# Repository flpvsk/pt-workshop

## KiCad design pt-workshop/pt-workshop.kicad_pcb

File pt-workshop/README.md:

### PTT

PT2399 adapter board for prototyping pedals.

[Schematic](./ptt-v1rev2.pdf)

#### Pins

1. +9V (Input)
2. GND (Input)
3. +4.5 (Input)
4. +5.0V (Output of the on-board 5V regulator)
5. GND (Input)
6. CLK (Ouptut of the PT2399 Clock pin, #5 on the chip)
7. Ref (Output of the PT2399 Ref pin, #2 on the chip)
8. GND (Input)
9. A In (Input for the audio signal)
10. A Out (Output of the processed audio signal)
11. GND (Input)
12. Ic In (Input, this pin is connected to the VCO pin #6 on
    PT2399, it controls delay time, see below for details);
13. Ic Out (Output of the Voltage-to-Current converter);
14. GND;
15. Vtime (Input of the Voltage-to-Current converter).

For minimum operation, please connect these pins. Keep in
mind for duplicate pins like GND, it's sufficient to just
connect one of the pins.

* `Pin 1`: +9V;
* `Pin 2`: GND;
* `Pin 3`: +4.5V;
* `Pin 9`: Audio In;
* `Pin 10`: Audio Out;
* `Pin 12`: Ic In. This pin controls delay time, see below
  for details.

#### Control delay time via a pot

`Ic In` pin (#12) on the adapter board is hooked up directly
to the control pin on the PT2399. The easiest way to vary
delay time is to connect this pin to ground via a
potentiometer, e.g. B100k.

The larger the resistance to GND the longer the delay time.

The minimum necessary resistance to GND on PT2399 startup is
2k. Otherwise the chip latches up. [See details in this Electrosmash article.](https://www.electrosmash.com/pt2399-analysis)

#### Control delay time via voltage

It is possible to control delay time of this board using
voltage instead of a potentiometer. There's an onboard
voltage-to-current converter. To use it, send control
voltage via `Vtime` pin and get the control current via the
`Ic Out` pin. Connect `Ic Out` to `Ic In` to control delay
time using `Vtime`. The lower `Vtime` the longer the delay
time would be.

#### Example minimal delay circuit with repeats

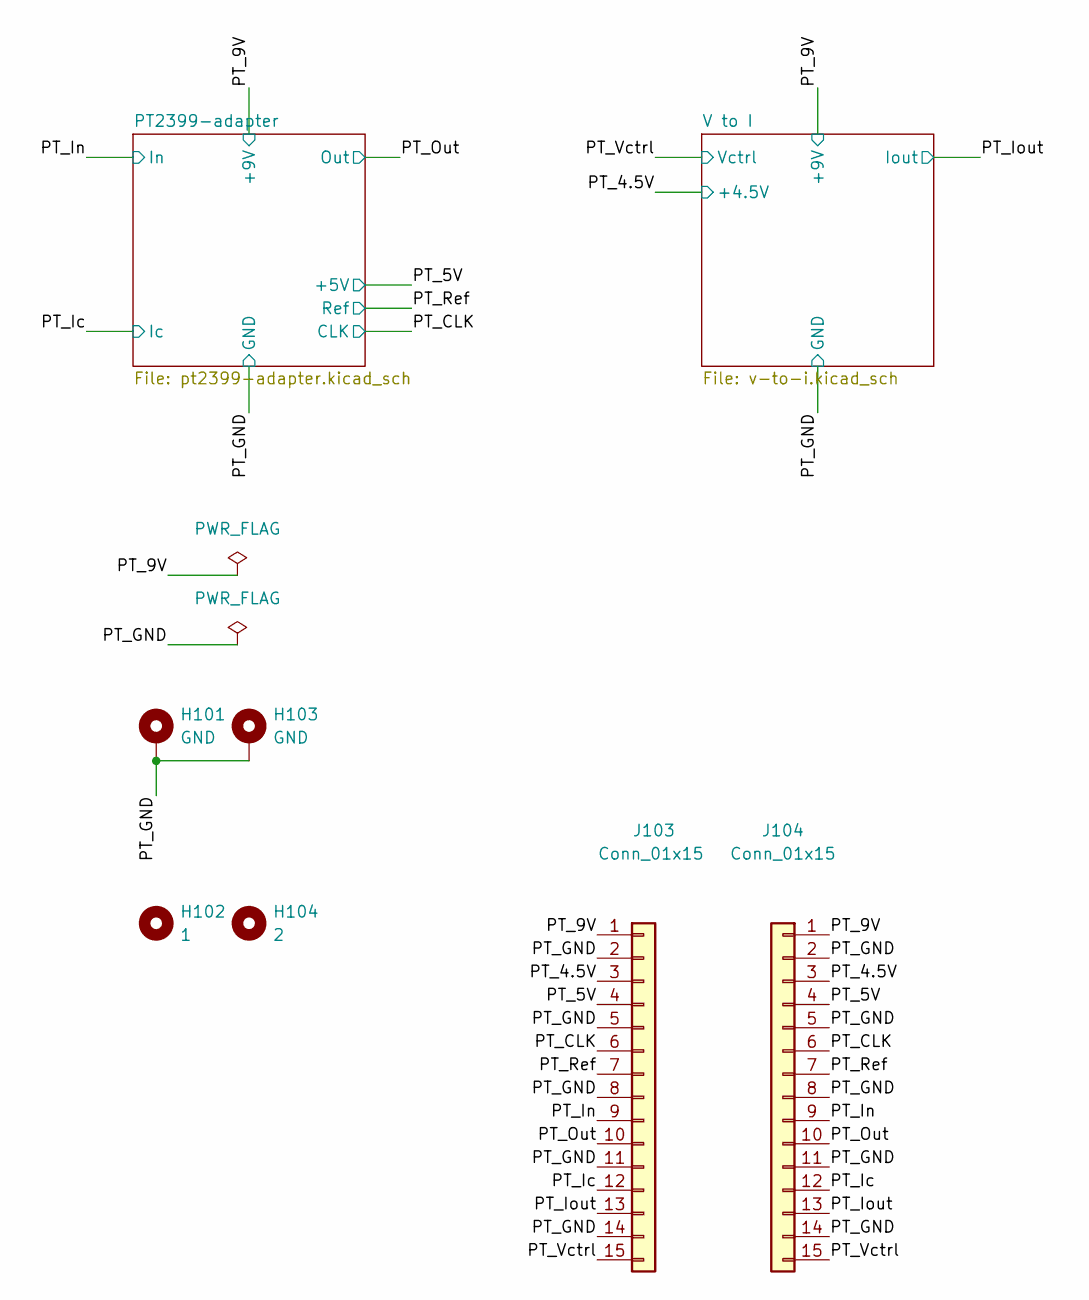
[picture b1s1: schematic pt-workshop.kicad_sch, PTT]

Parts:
H101, H103: GND; MountingHole_3.2mm_M3_ISO14580_Pad
H102: 1; MountingHole_3.2mm_M3
H104: 2; MountingHole_3.2mm_M3
J103, J104: Conn_01x15; PinSocket_1x15_P2.54mm_Vertical

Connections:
/PT_4.5V: J103.3, J104.3; also elsewhere on the board
/PT_5V: J103.4, J104.4; also elsewhere on the board
/PT_9V: J103.1, J104.1; also elsewhere on the board
/PT_CLK: J103.6, J104.6; also elsewhere on the board
/PT_GND: H101.1, H103.1, J103.2, J103.5, J103.8, J103.11, J103.14, J104.2, J104.5, J104.8, J104.11, J104.14; also elsewhere on the board
/PT_Ic: J103.12, J104.12; also elsewhere on the board
/PT_In: J103.9, J104.9; also elsewhere on the board
/PT_Iout: J103.13, J104.13; also elsewhere on the board
/PT_Out: J103.10, J104.10; also elsewhere on the board
/PT_Ref: J103.7, J104.7; also elsewhere on the board
/PT_Vctrl: J103.15, J104.15; also elsewhere on the board

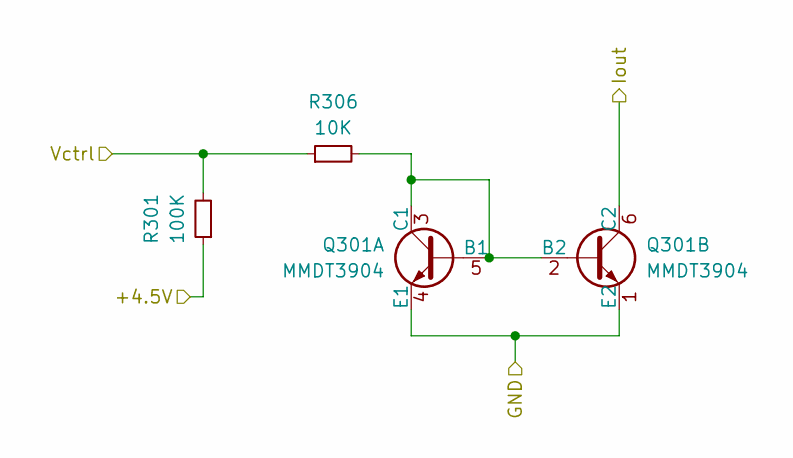
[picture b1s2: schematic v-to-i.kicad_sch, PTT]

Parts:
Q301: MMDT3904; SOT-363_SC-70-6_Handsoldering; LCSC C41375125
R301: 100K; R_0603_1608Metric_Pad0.98x0.95mm_HandSolder; LCSC C25803
R306: 10K; R_0603_1608Metric_Pad0.98x0.95mm_HandSolder; LCSC C25804

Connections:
/PT_4.5V: R301.1; also elsewhere on the board
/PT_GND: Q301.1 (E2), Q301.4 (E1); also elsewhere on the board
/PT_Iout: Q301.6 (C2); also elsewhere on the board
/PT_Vctrl: R301.2, R306.1; also elsewhere on the board
unnamed: Q301.2 (B2), Q301.3 (C1), Q301.5 (B1), R306.2

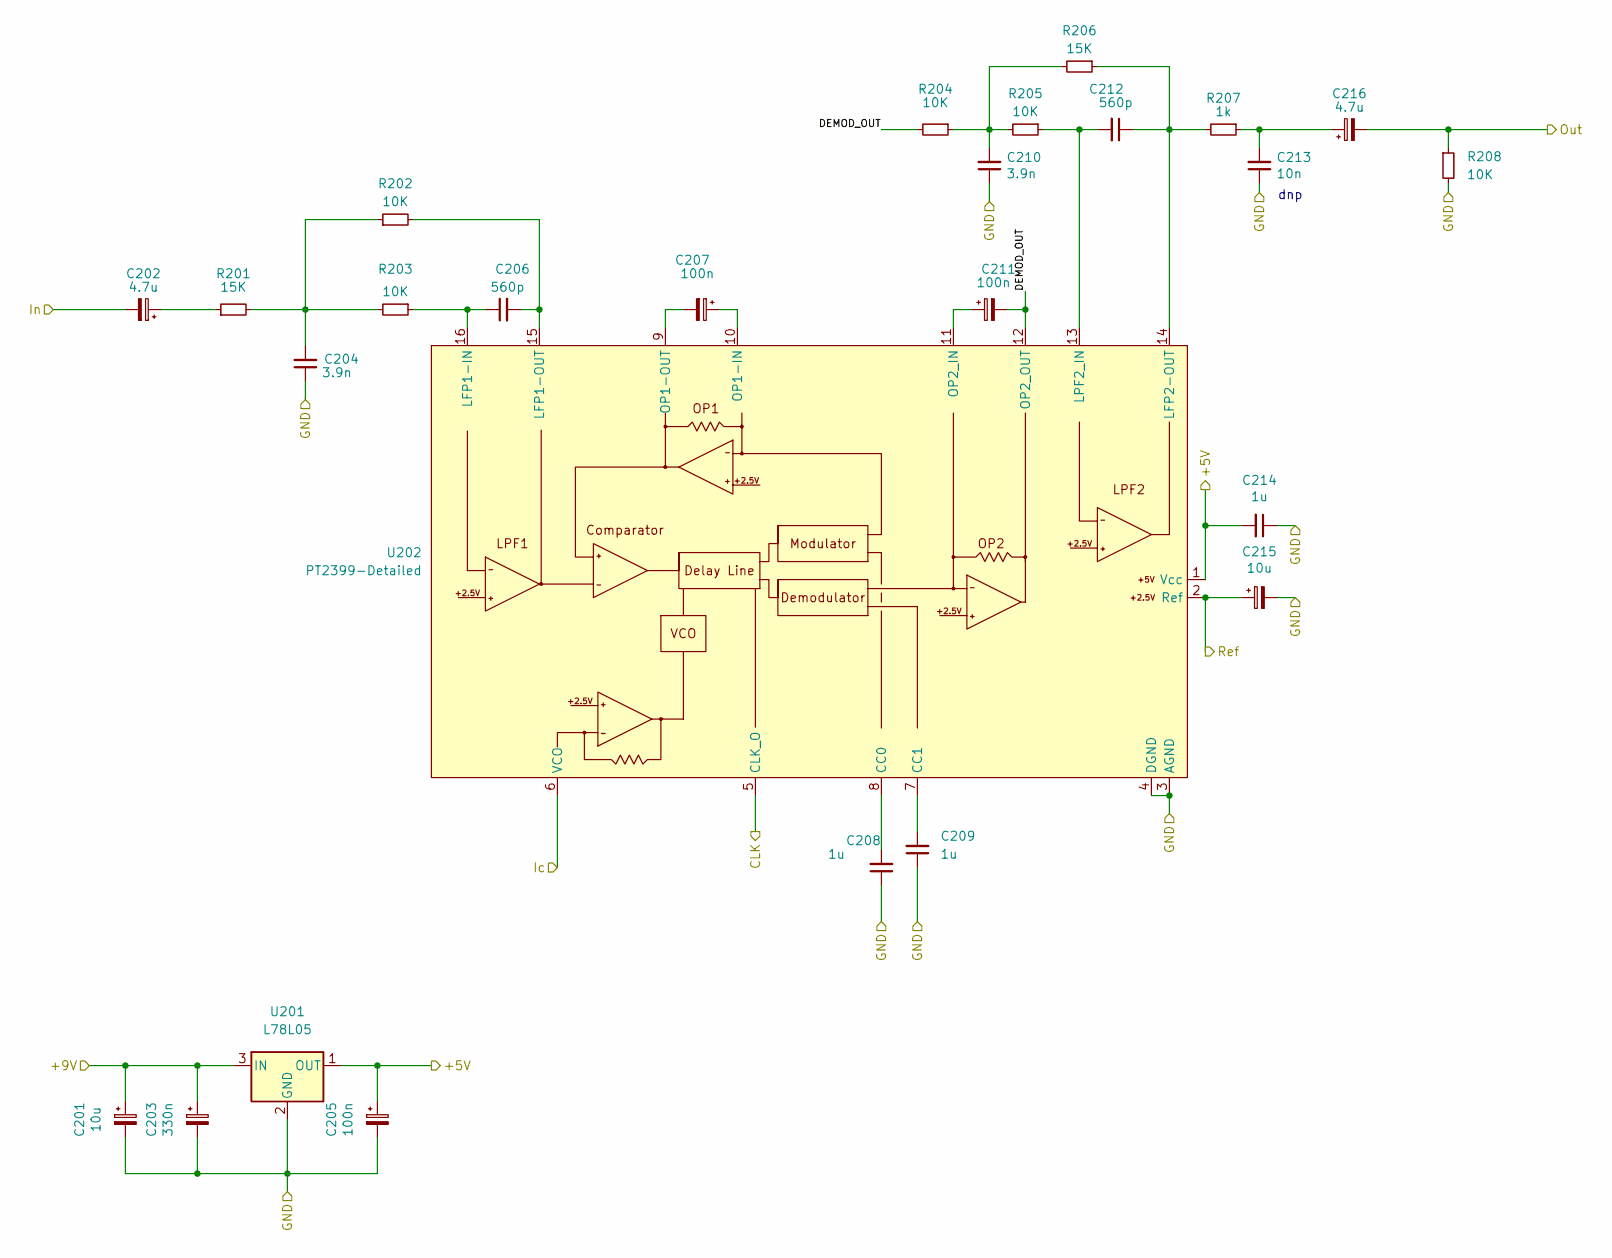
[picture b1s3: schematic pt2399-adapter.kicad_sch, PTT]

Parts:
C201, C215: 10u; CP_EIA-3216-10_Kemet-I_Pad1.58x1.35mm_HandSolder; LCSC C128253
C202, C216: 4.7u; CP_Elec_4x5.4; LCSC C5246584
C203: 330n; CP_EIA-3216-10_Kemet-I_Pad1.58x1.35mm_HandSolder; LCSC C212667
C204, C210: 3.9n; C_0603_1608Metric_Pad1.08x0.95mm_HandSolder; LCSC C415537
C205: 100n; CP_EIA-3216-10_Kemet-I_Pad1.58x1.35mm_HandSolder; LCSC C1952859
C206, C212: 560p; C_0603_1608Metric_Pad1.08x0.95mm_HandSolder; LCSC C694498
C207, C211: 100n; CP_Elec_4x5.4; Mouser 710-865080440002
C208, C209, C214: 1u; C_0603_1608Metric_Pad1.08x0.95mm_HandSolder; LCSC C15849
C213: 10n; C_0603_1608Metric_Pad1.08x0.95mm_HandSolder; LCSC C3836718
R201, R206: 15K; R_0603_1608Metric_Pad0.98x0.95mm_HandSolder; LCSC C22809
R202, R203, R204, R205, R208: 10K; R_0603_1608Metric_Pad0.98x0.95mm_HandSolder; LCSC C25804
R207: 1k; R_0603_1608Metric_Pad0.98x0.95mm_HandSolder; LCSC C21190
U201: L78L05; SOT-89-3; LCSC C42738
U202: PT2399-Detailed; SOIC-16_3.9x9.9mm_P1.27mm; LCSC C126407

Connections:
/PT2399-adapter/DEMOD_OUT: C211.2, R204.2, U202.12 (OP2_OUT)
/PT_5V: C205.1, C214.2, U201.1 (OUT), U202.1 (Vcc); also elsewhere on the board
/PT_9V: C201.1, C203.1, U201.3 (IN); also elsewhere on the board
/PT_CLK: U202.5 (CLK_O); also elsewhere on the board
/PT_GND: C201.2, C203.2, C204.1, C205.2, C208.1, C209.1, C210.1, C213.1, C214.1, C215.2, R208.2, U201.2 (GND), U202.3 (AGND), U202.4 (DGND); also elsewhere on the board
/PT_Ic: U202.6 (VCO); also elsewhere on the board
/PT_In: C202.2; also elsewhere on the board
/PT_Out: C216.2, R208.1; also elsewhere on the board
/PT_Ref: C215.1, U202.2 (Ref); also elsewhere on the board
unnamed: C202.1, R201.1
unnamed: C204.2, R201.2, R202.1, R203.2
unnamed: C206.1, R203.1, U202.16 (LFP1-IN)
unnamed: C206.2, R202.2, U202.15 (LFP1-OUT)
unnamed: C207.1, U202.10 (OP1-IN)
unnamed: C207.2, U202.9 (OP1-OUT)
unnamed: C208.2, U202.8 (CC0)
unnamed: C209.2, U202.7 (CC1)
unnamed: C210.2, R204.1, R205.2, R206.2
unnamed: C211.1, U202.11 (OP2_IN)
unnamed: C212.1, R206.1, R207.2, U202.14 (LFP2-OUT)
unnamed: C212.2, R205.1, U202.13 (LPF2_IN)
unnamed: C213.2, C216.1, R207.1

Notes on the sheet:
dnp

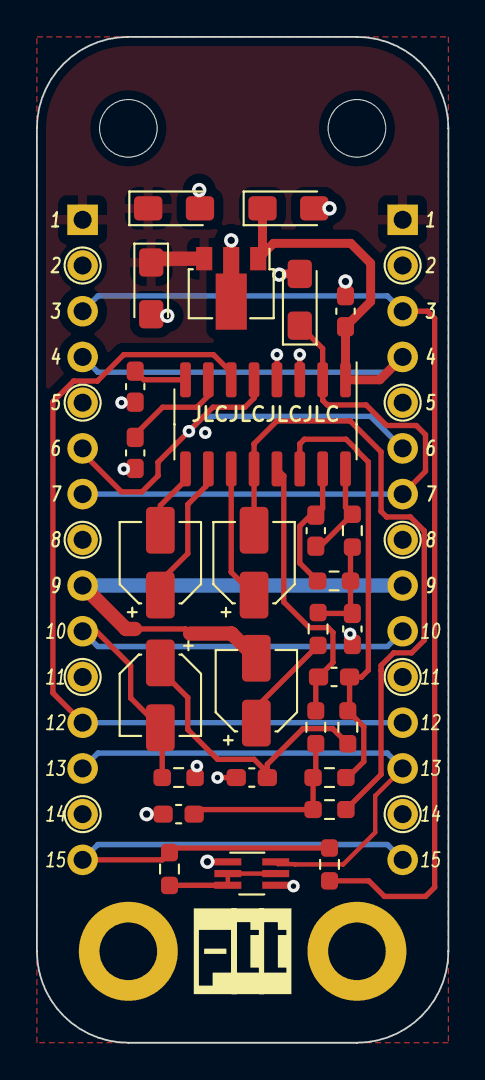
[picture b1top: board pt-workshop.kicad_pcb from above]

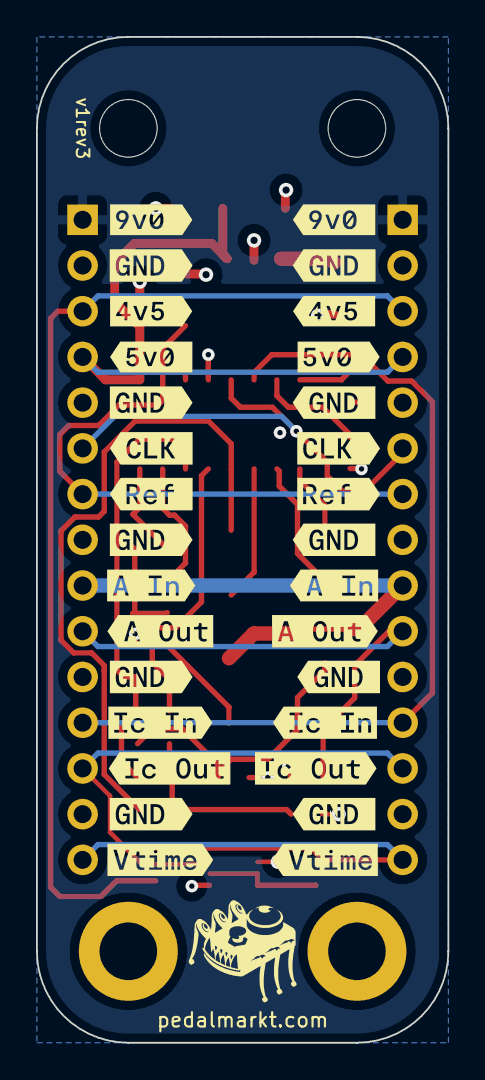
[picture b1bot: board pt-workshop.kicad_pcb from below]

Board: 4 copper layers, 22.9 x 55.9 mm, 66 parts (30 on the bottom side), 26 nets.

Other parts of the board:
kibuzzard-65E1A759: G***; kibuzzard-65E1A759
kibuzzard-68A2FE0E: G***; kibuzzard-68A2FE0E
kibuzzard-68A2FE01: G***; kibuzzard-68A2FE01
kibuzzard-68A2FE1E: G***; kibuzzard-68A2FE1E
kibuzzard-68A2FE2B: G***; kibuzzard-68A2FE2B
kibuzzard-68A2FE3C: G***; kibuzzard-68A2FE3C
kibuzzard-68A2FE4A: G***; kibuzzard-68A2FE4A
kibuzzard-68A2FE4F: G***; kibuzzard-68A2FE4F
kibuzzard-68A2FE5C: G***; kibuzzard-68A2FE5C
kibuzzard-68A2FE06: G***; kibuzzard-68A2FE06
kibuzzard-68A2FE6B: G***; kibuzzard-68A2FE6B
kibuzzard-68A2FE7B: G***; kibuzzard-68A2FE7B
kibuzzard-68A2FE8A: G***; kibuzzard-68A2FE8A
kibuzzard-68A2FE8F: G***; kibuzzard-68A2FE8F
kibuzzard-68A2FE18: G***; kibuzzard-68A2FE18
kibuzzard-68A2FE25: G***; kibuzzard-68A2FE25
kibuzzard-68A2FE30: G***; kibuzzard-68A2FE30
kibuzzard-68A2FE36: G***; kibuzzard-68A2FE36
kibuzzard-68A2FE41: G***; kibuzzard-68A2FE41
kibuzzard-68A2FE46: G***; kibuzzard-68A2FE46
kibuzzard-68A2FE55: G***; kibuzzard-68A2FE55
kibuzzard-68A2FE62: G***; kibuzzard-68A2FE62
kibuzzard-68A2FE67: G***; kibuzzard-68A2FE67
kibuzzard-68A2FE71: G***; kibuzzard-68A2FE71
kibuzzard-68A2FE76: G***; kibuzzard-68A2FE76
kibuzzard-68A2FE80: G***; kibuzzard-68A2FE80
kibuzzard-68A2FE85: G***; kibuzzard-68A2FE85
kibuzzard-68A2FF1E: G***; kibuzzard-68A2FF1E
kibuzzard-68A2FF07: G***; kibuzzard-68A2FF07
kibuzzard-68A2FF19: G***; kibuzzard-68A2FF19
kibuzzard-68A2FF23: G***; kibuzzard-68A2FF23

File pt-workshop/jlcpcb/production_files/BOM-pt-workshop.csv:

Comment,Designator,Footprint,LCSC
PT2399-Detailed,U202,SOIC-16_3.9x9.9mm_P1.27mm,C126407
10u,"C201,C215",CP_EIA-3216-10_Kemet-I_Pad1.58x1.35mm_HandSolder,C128254
1u,"C208,C209,C214",C_0603_1608Metric_Pad1.08x0.95mm_HandSolder,C15849
100n,C205,CP_EIA-3216-10_Kemet-I_Pad1.58x1.35mm_HandSolder,C1952859
1k,R207,R_0603_1608Metric_Pad0.98x0.95mm_HandSolder,C21190
330n,C203,CP_EIA-3216-10_Kemet-I_Pad1.58x1.35mm_HandSolder,C212667
15K,"R201,R206",R_0603_1608Metric_Pad0.98x0.95mm_HandSolder,C22809
100K,R301,R_0603_1608Metric_Pad0.98x0.95mm_HandSolder,C25803
10K,"R202,R203,R204,R205,R208,R306",R_0603_1608Metric_Pad0.98x0.95mm_HandSolder,C25804
10n,C213,C_0603_1608Metric_Pad1.08x0.95mm_HandSolder,C3836718
MMDT3904,Q301,SOT-363_SC-70-6_Handsoldering,C41375125
3.9n,"C204,C210",C_0603_1608Metric_Pad1.08x0.95mm_HandSolder,C415537
L78L05,U201,SOT-89-3,C42738
560p,"C206,C212",C_0603_1608Metric_Pad1.08x0.95mm_HandSolder,C694498
4.7u,"C202,C216",CP_Elec_4x5.4,C72511
GND,H103,MountingHole_3.2mm_M3_ISO14580_Pad,
1,H102,MountingHole_3.2mm_M3,
GND,H101,MountingHole_3.2mm_M3_ISO14580_Pad,
2,H104,MountingHole_3.2mm_M3,
100n,C207,CP_Elec_4x5.4,
Conn_01x15,J103,PinSocket_1x15_P2.54mm_Vertical,
100n,C211,CP_Elec_4x5.4,
Conn_01x15,J104,PinSocket_1x15_P2.54mm_Vertical,

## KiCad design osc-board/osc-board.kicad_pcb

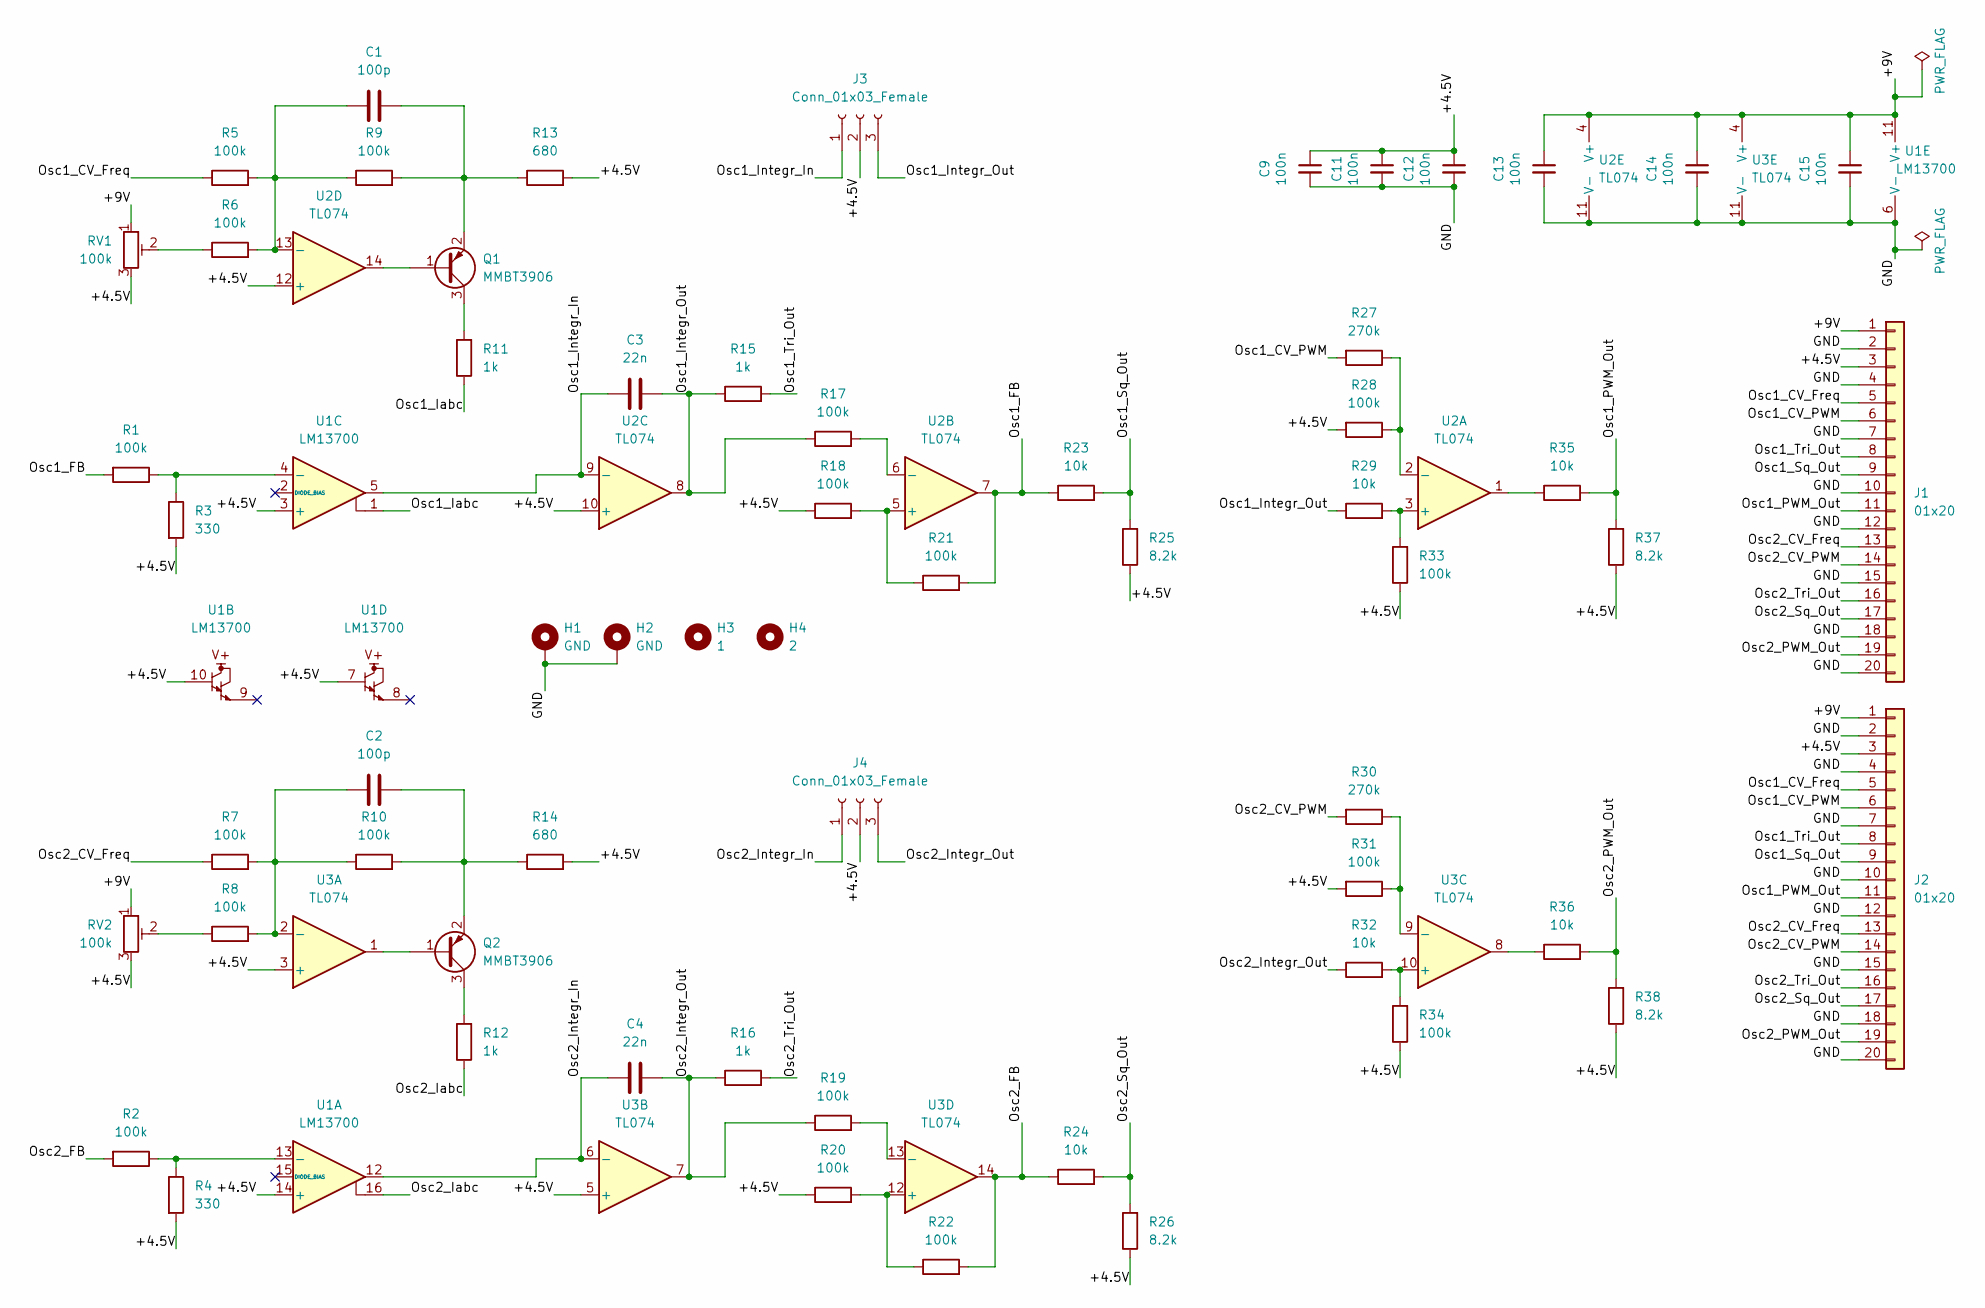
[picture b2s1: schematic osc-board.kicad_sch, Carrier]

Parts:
C1, C2: 100p; C_0603_1608Metric_Pad1.08x0.95mm_HandSolder; Mouser 581-0603YC101KAT2A
C3, C4: 22n; C_0603_1608Metric_Pad1.08x0.95mm_HandSolder; Mouser 77-VJ0603Y223JXJAC
C9, C11, C12, C13, C14, C15: 100n; C_0603_1608Metric_Pad1.08x0.95mm_HandSolder; LCSC C14663
H1, H2: GND; MountingHole_3.2mm_M3_ISO14580_Pad
H3: 1; MountingHole_3.2mm_M3
H4: 2; MountingHole_3.2mm_M3
J1, J2: 01x20; PinHeader_1x20_P2.54mm_Vertical
J3, J4: Conn_01x03_Female; PinHeader_1x03_P2.54mm_Vertical
Q1, Q2: MMBT3906; SOT-23; LCSC C727128
R1, R2, R5, R6, R7, R8, R9, R10, R17, R18, R19, R20, R21, R22, R28, R31, R33, R34: 100k; R_0603_1608Metric_Pad0.98x0.95mm_HandSolder; Mouser 71-RCS0603100KFKEA
R3, R4: 330; R_0603_1608Metric_Pad0.98x0.95mm_HandSolder; Mouser 652-CMP0603-FX-3300L
R11, R12, R15, R16: 1k; R_0603_1608Metric_Pad0.98x0.95mm_HandSolder; Mouser 755-ESR03EZPF1001
R13, R14: 680; R_0603_1608Metric_Pad0.98x0.95mm_HandSolder; Mouser 279-CRGP0603F680R
R23, R24, R29, R32, R35, R36: 10k; R_0603_1608Metric_Pad0.98x0.95mm_HandSolder; Mouser 279-CRGP0603F10K
R25, R26, R37, R38: 8.2k; R_0603_1608Metric_Pad0.98x0.95mm_HandSolder; Mouser 279-CRGP0603F8K2
R27, R30: 270k; R_0603_1608Metric_Pad0.98x0.95mm_HandSolder; Mouser 279-CRGP0603F270K
RV1, RV2: 100k; Potentiometer_Bourns_3314J_Vertical; LCSC C51284
U1: LM13700; SOP-16_4.55x10.3mm_P1.27mm; LCSC C5160094
U2, U3: TL074; SOIC-14_3.9x8.7mm_P1.27mm; LCSC C6963

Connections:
/+4.5V: C9.1, C11.1, C12.1, J1.3, J2.3, J3.2, J4.2, R3.2, R4.2, R13.2, R14.2, R18.1, R20.1, R25.1, R26.1, R28.2, R31.2, R33.1, R34.1, R37.1, R38.1, RV1.3, RV2.3, U1.3 (+), U1.7, U1.10, U1.14 (+), U2.10 (+), U2.12 (+), U3.3 (+), U3.5 (+)
/+9V: C13.1, C14.1, C15.1, J1.1, J2.1, RV1.1, RV2.1, U1.11 (V+), U2.4 (V+), U3.4 (V+)
/GND: C9.2, C11.2, C12.2, C13.2, C14.2, C15.2, H1.1, H2.1, J1.2, J1.4, J1.7, J1.10, J1.12, J1.15, J1.18, J1.20, J2.2, J2.4, J2.7, J2.10, J2.12, J2.15, J2.18, J2.20, U1.6 (V-), U2.11 (V-), U3.11 (V-)
/Osc1_CV_Freq: J1.5, J2.5, R5.1
/Osc1_CV_PWM: J1.6, J2.6, R27.2
/Osc1_FB: R1.2, R21.2, R23.1, U2.7
/Osc1_Iabc: R11.1, U1.1
/Osc1_Integr_In: C3.1, J3.1, U1.5, U2.9 (-)
/Osc1_Integr_Out: C3.2, J3.3, R15.1, R17.1, R29.1, U2.8
/Osc1_PWM_Out: J1.11, J2.11, R35.2, R37.2
/Osc1_Sq_Out: J1.9, J2.9, R23.2, R25.2
/Osc1_Tri_Out: J1.8, J2.8, R15.2
/Osc2_CV_Freq: J1.13, J2.13, R7.1
/Osc2_CV_PWM: J1.14, J2.14, R30.2
/Osc2_FB: R2.2, R22.2, R24.1, U3.14
/Osc2_Iabc: R12.1, U1.16
/Osc2_Integr_In: C4.1, J4.1, U1.12, U3.6 (-)
/Osc2_Integr_Out: C4.2, J4.3, R16.1, R19.1, R32.1, U3.7
/Osc2_PWM_Out: J1.19, J2.19, R36.2, R38.2
/Osc2_Sq_Out: J1.17, J2.17, R24.2, R26.2
/Osc2_Tri_Out: J1.16, J2.16, R16.2
unnamed: C1.1, R5.2, R6.2, R9.1, U2.13 (-)
unnamed: C1.2, Q1.2 (E), R9.2, R13.1
unnamed: C2.1, R7.2, R8.2, R10.1, U3.2 (-)
unnamed: C2.2, Q2.2 (E), R10.2, R14.1
unnamed: Q1.1 (B), U2.14
unnamed: Q1.3 (C), R11.2
unnamed: Q2.1 (B), U3.1
unnamed: Q2.3 (C), R12.2
unnamed: R1.1, R3.1, U1.4 (-)
unnamed: R2.1, R4.1, U1.13 (-)
unnamed: R6.1, RV1.2
unnamed: R8.1, RV2.2
unnamed: R17.2, U2.6 (-)
unnamed: R18.2, R21.1, U2.5 (+)
unnamed: R19.2, U3.13 (-)
unnamed: R20.2, R22.1, U3.12 (+)
unnamed: R27.1, R28.1, U2.2 (-)
unnamed: R29.2, R33.2, U2.3 (+)
unnamed: R30.1, R31.1, U3.9 (-)
unnamed: R32.2, R34.2, U3.10 (+)
unnamed: R35.1, U2.1
unnamed: R36.1, U3.8

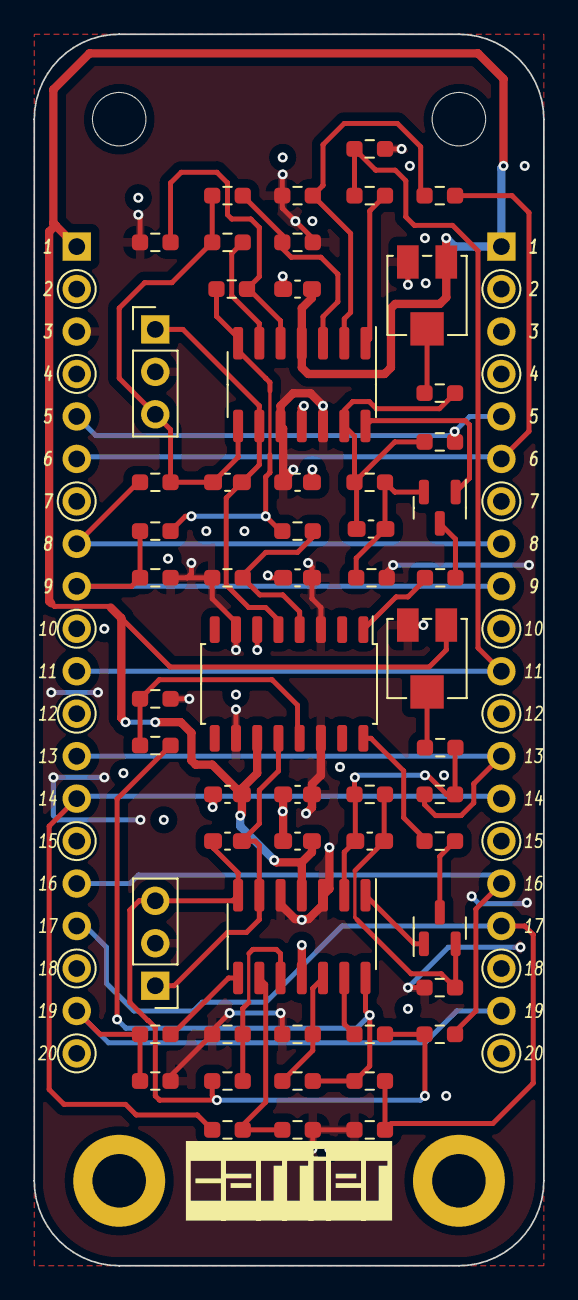
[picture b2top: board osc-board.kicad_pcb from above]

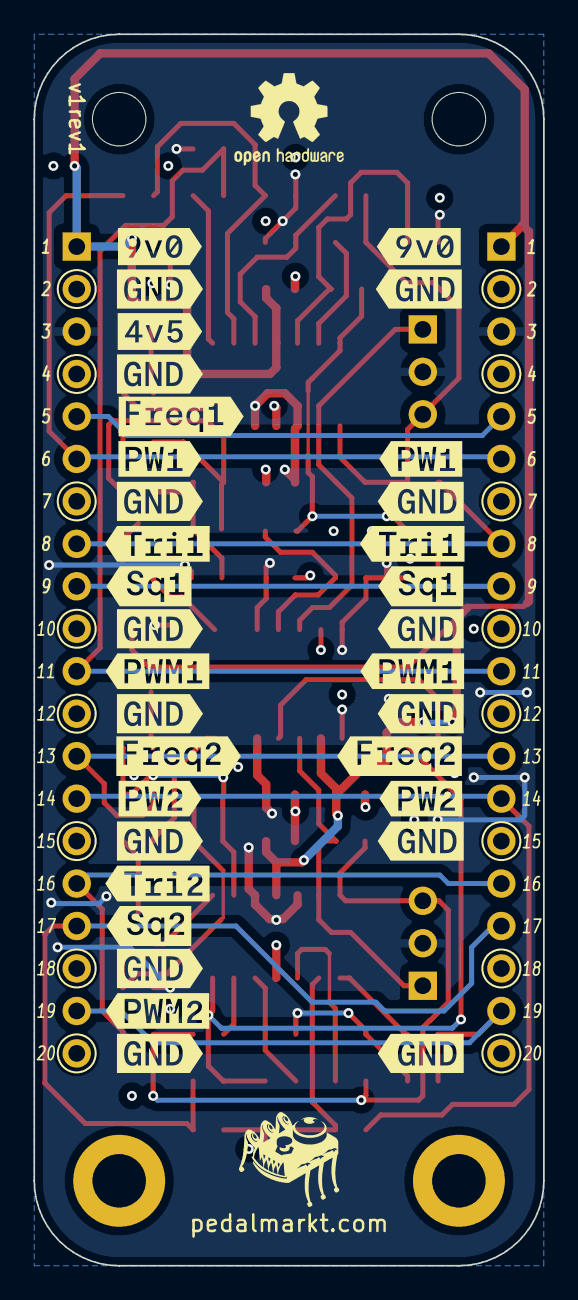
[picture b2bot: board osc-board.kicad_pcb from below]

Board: 4 copper layers, 30.5 x 73.7 mm, 97 parts (33 on the bottom side), 43 nets.

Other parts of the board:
kibuzzard-672CA10D: G***; kibuzzard-672CA10D
kibuzzard-672CA24E: G***; kibuzzard-672CA24E
kibuzzard-672CA102: G***; kibuzzard-672CA102
kibuzzard-672CA109, kibuzzard-672CA109#2, kibuzzard-672CA109#3, kibuzzard-672CA109#4, kibuzzard-672CA109#5, kibuzzard-672CA109#6, kibuzzard-672CA109#7, kibuzzard-672CA109#8: G***; kibuzzard-672CA109
kibuzzard-672CA252, kibuzzard-672CA252#2, kibuzzard-672CA252#3, kibuzzard-672CA252#4, kibuzzard-672CA252#5, kibuzzard-672CA252#6: G***; kibuzzard-672CA252
kibuzzard-6771A5DA: G***; kibuzzard-6771A5DA
kibuzzard-6771A5FD: G***; kibuzzard-6771A5FD
kibuzzard-6771A9AC: G***; kibuzzard-6771A9AC
kibuzzard-6771A9DB: G***; kibuzzard-6771A9DB
kibuzzard-6771A9DE: G***; kibuzzard-6771A9DE
kibuzzard-6771A9ED: G***; kibuzzard-6771A9ED
kibuzzard-6771A96D: G***; kibuzzard-6771A96D
kibuzzard-6771A890: G***; kibuzzard-6771A890
kibuzzard-6771A943: G***; kibuzzard-6771A943
kibuzzard-6771A949: G***; kibuzzard-6771A949
kibuzzard-6771A969: G***; kibuzzard-6771A969
kibuzzard-6771AA0E: G***; kibuzzard-6771AA0E
kibuzzard-6771AA3E: G***; kibuzzard-6771AA3E
kibuzzard-6771AA6F: G***; kibuzzard-6771AA6F
kibuzzard-6771AA16: G***; kibuzzard-6771AA16
kibuzzard-6771AA21: G***; kibuzzard-6771AA21
kibuzzard-6776C4B6: G***; kibuzzard-6776C4B6

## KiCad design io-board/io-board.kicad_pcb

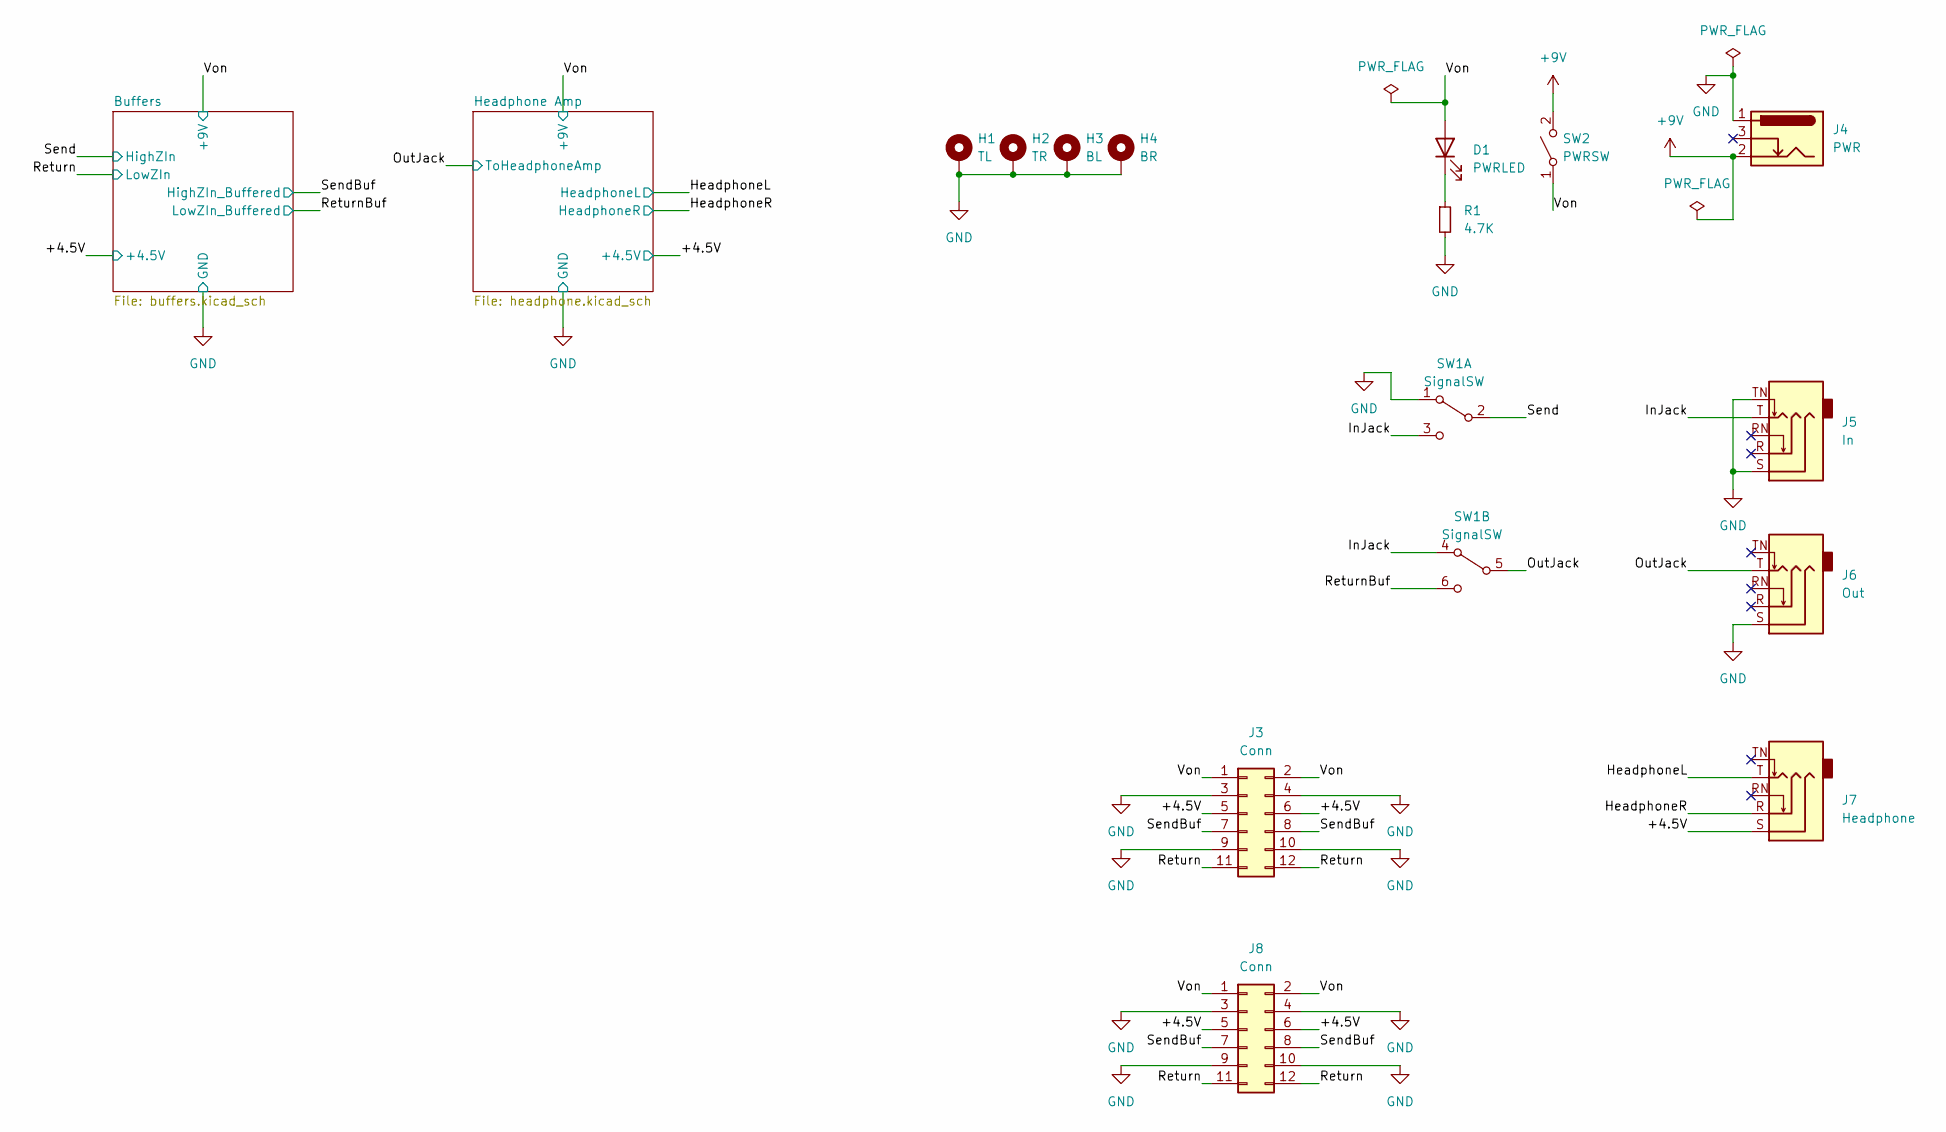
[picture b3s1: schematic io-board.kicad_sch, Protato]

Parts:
D1: PWRLED; LED_1206_3216Metric_Pad1.42x1.75mm_HandSolder; Mouser 710-150080RS75000
H1: TL; MountingHole_3.2mm_M3_Pad_Via
H2: TR; MountingHole_3.2mm_M3_Pad_Via
H3: BL; MountingHole_3.2mm_M3_Pad_Via
H4: BR; MountingHole_3.2mm_M3_Pad_Via
J3, J8: Conn; PinHeader_2x06_P2.54mm_Vertical
J4: PWR; BarrelJack_GCT_DCJ200-10-A_Horizontal
J5: In; tayda-6mm35-jack-pcb-compact
J6: Out; tayda-6mm35-jack-pcb-compact
J7: Headphone; Jack_3.5mm_CUI_SJ1-3525N_Horizontal; Mouser 490-SJ1-3525N
R1: 4.7K; R_0603_1608Metric_Pad0.98x0.95mm_HandSolder; LCSC C23162
SW1: SignalSW; DPDT.LUGS
SW2: PWRSW; SPDT.LUGS

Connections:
+9V: J4.2, SW2.2 (B)
/+4.5V: J3.5, J3.6, J7.S, J8.5, J8.6; also elsewhere on the board
/HeadphoneL: J7.T; also elsewhere on the board
/HeadphoneR: J7.R; also elsewhere on the board
/InJack: J5.T, SW1.3 (C), SW1.4 (A)
/OutJack: J6.T, SW1.5 (B); also elsewhere on the board
/Return: J3.11, J3.12, J8.11, J8.12; also elsewhere on the board
/ReturnBuf: SW1.6 (C); also elsewhere on the board
/Send: SW1.2 (B); also elsewhere on the board
/SendBuf: J3.7, J3.8, J8.7, J8.8; also elsewhere on the board
/Von: D1.2 (A), J3.1, J3.2, J8.1, J8.2, SW2.1 (A); also elsewhere on the board
GND: H1.1, H2.1, H3.1, H4.1, J3.3, J3.4, J3.9, J3.10, J4.1, J5.S, J5.TN, J6.S, J8.3, J8.4, J8.9, J8.10, R1.2, SW1.1 (A); also elsewhere on the board
unnamed: D1.1 (K), R1.1

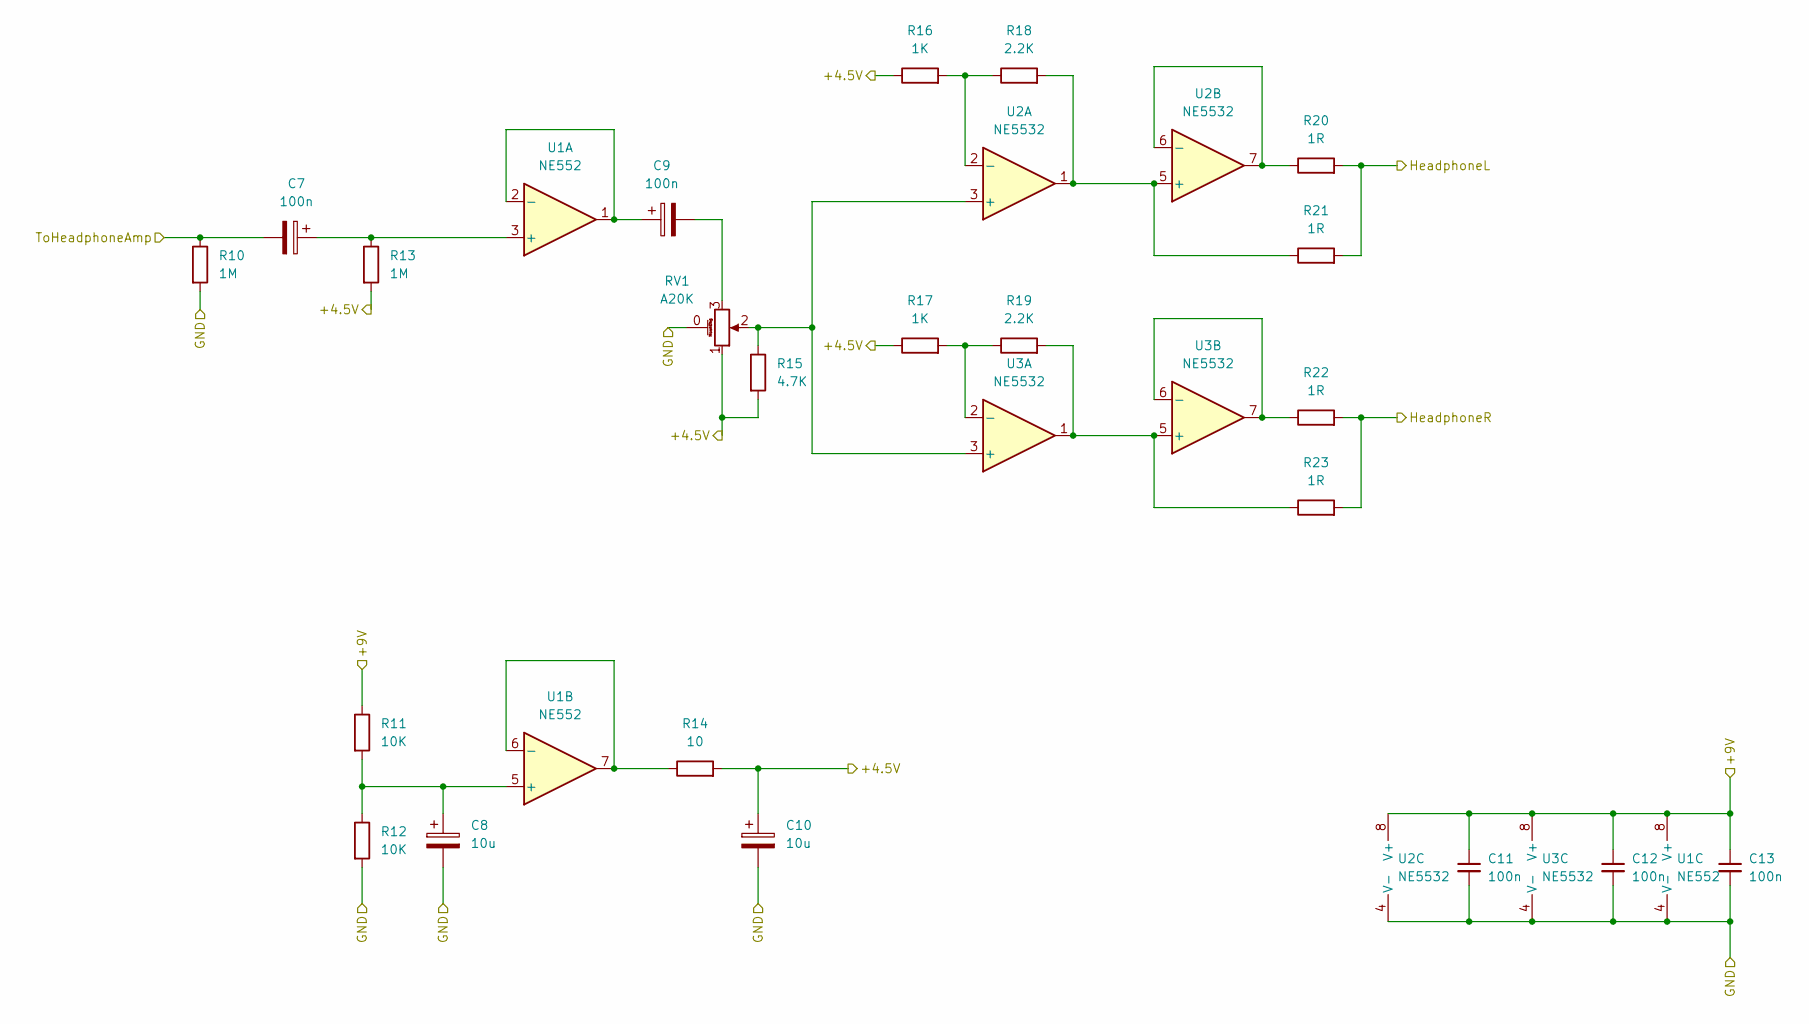
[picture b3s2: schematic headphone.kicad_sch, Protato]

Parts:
C7, C9: 100n; CP_Elec_4x5.4; LCSC C271438
C8: 10u; CP_Elec_4x5.4; Mouser 710-865080340001
C10: 10u; CP_Elec_4x5.4; LCSC C240540
C11, C12, C13: 100n; C_0603_1608Metric_Pad1.08x0.95mm_HandSolder; LCSC C497032
R10, R13: 1M; R_0603_1608Metric_Pad0.98x0.95mm_HandSolder; LCSC C105578
R11, R12: 10K; R_0603_1608Metric_Pad0.98x0.95mm_HandSolder; LCSC C25804
R14: 10; R_0603_1608Metric_Pad0.98x0.95mm_HandSolder; LCSC C22859
R15: 4.7K; R_0603_1608Metric_Pad0.98x0.95mm_HandSolder; LCSC C23162
R16, R17: 1K; R_0603_1608Metric_Pad0.98x0.95mm_HandSolder; LCSC C21190
R18, R19: 2.2K; R_0603_1608Metric_Pad0.98x0.95mm_HandSolder; LCSC C4190
R20, R21, R22, R23: 1R; R_0603_1608Metric_Pad0.98x0.95mm_HandSolder; LCSC C22936
RV1: A20K; V3_TRIM_R0904NB10KL-Keepout
U1: NE552; SOIC-8_3.9x4.9mm_P1.27mm; LCSC C7426
U2, U3: NE5532; SOIC-8_3.9x4.9mm_P1.27mm; LCSC C7426

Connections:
/+4.5V: C10.1, R13.2, R14.2, R15.2, R16.1, R17.1, RV1.1; also elsewhere on the board
/HeadphoneL: R20.2, R21.2; also elsewhere on the board
/HeadphoneR: R22.2, R23.2; also elsewhere on the board
/OutJack: C7.2, R10.1; also elsewhere on the board
/Von: C11.1, C12.1, C13.1, R11.1, U1.8 (V+), U2.8 (V+), U3.8 (V+); also elsewhere on the board
GND: C8.2, C10.2, C11.2, C12.2, C13.2, R10.2, R12.2, RV1.0 (ShieldPin), U1.4 (V-), U2.4 (V-), U3.4 (V-); also elsewhere on the board
unnamed: C7.1, R13.1, U1.3 (+)
unnamed: C8.1, R11.2, R12.1, U1.5 (+)
unnamed: C9.1, U1.1, U1.2 (-)
unnamed: C9.2, RV1.3
unnamed: R14.1, U1.6 (-), U1.7
unnamed: R15.1, RV1.2, U2.3 (+), U3.3 (+)
unnamed: R16.2, R18.1, U2.2 (-)
unnamed: R17.2, R19.1, U3.2 (-)
unnamed: R18.2, R21.1, U2.1, U2.5 (+)
unnamed: R19.2, R23.1, U3.1, U3.5 (+)
unnamed: R20.1, U2.6 (-), U2.7
unnamed: R22.1, U3.6 (-), U3.7
